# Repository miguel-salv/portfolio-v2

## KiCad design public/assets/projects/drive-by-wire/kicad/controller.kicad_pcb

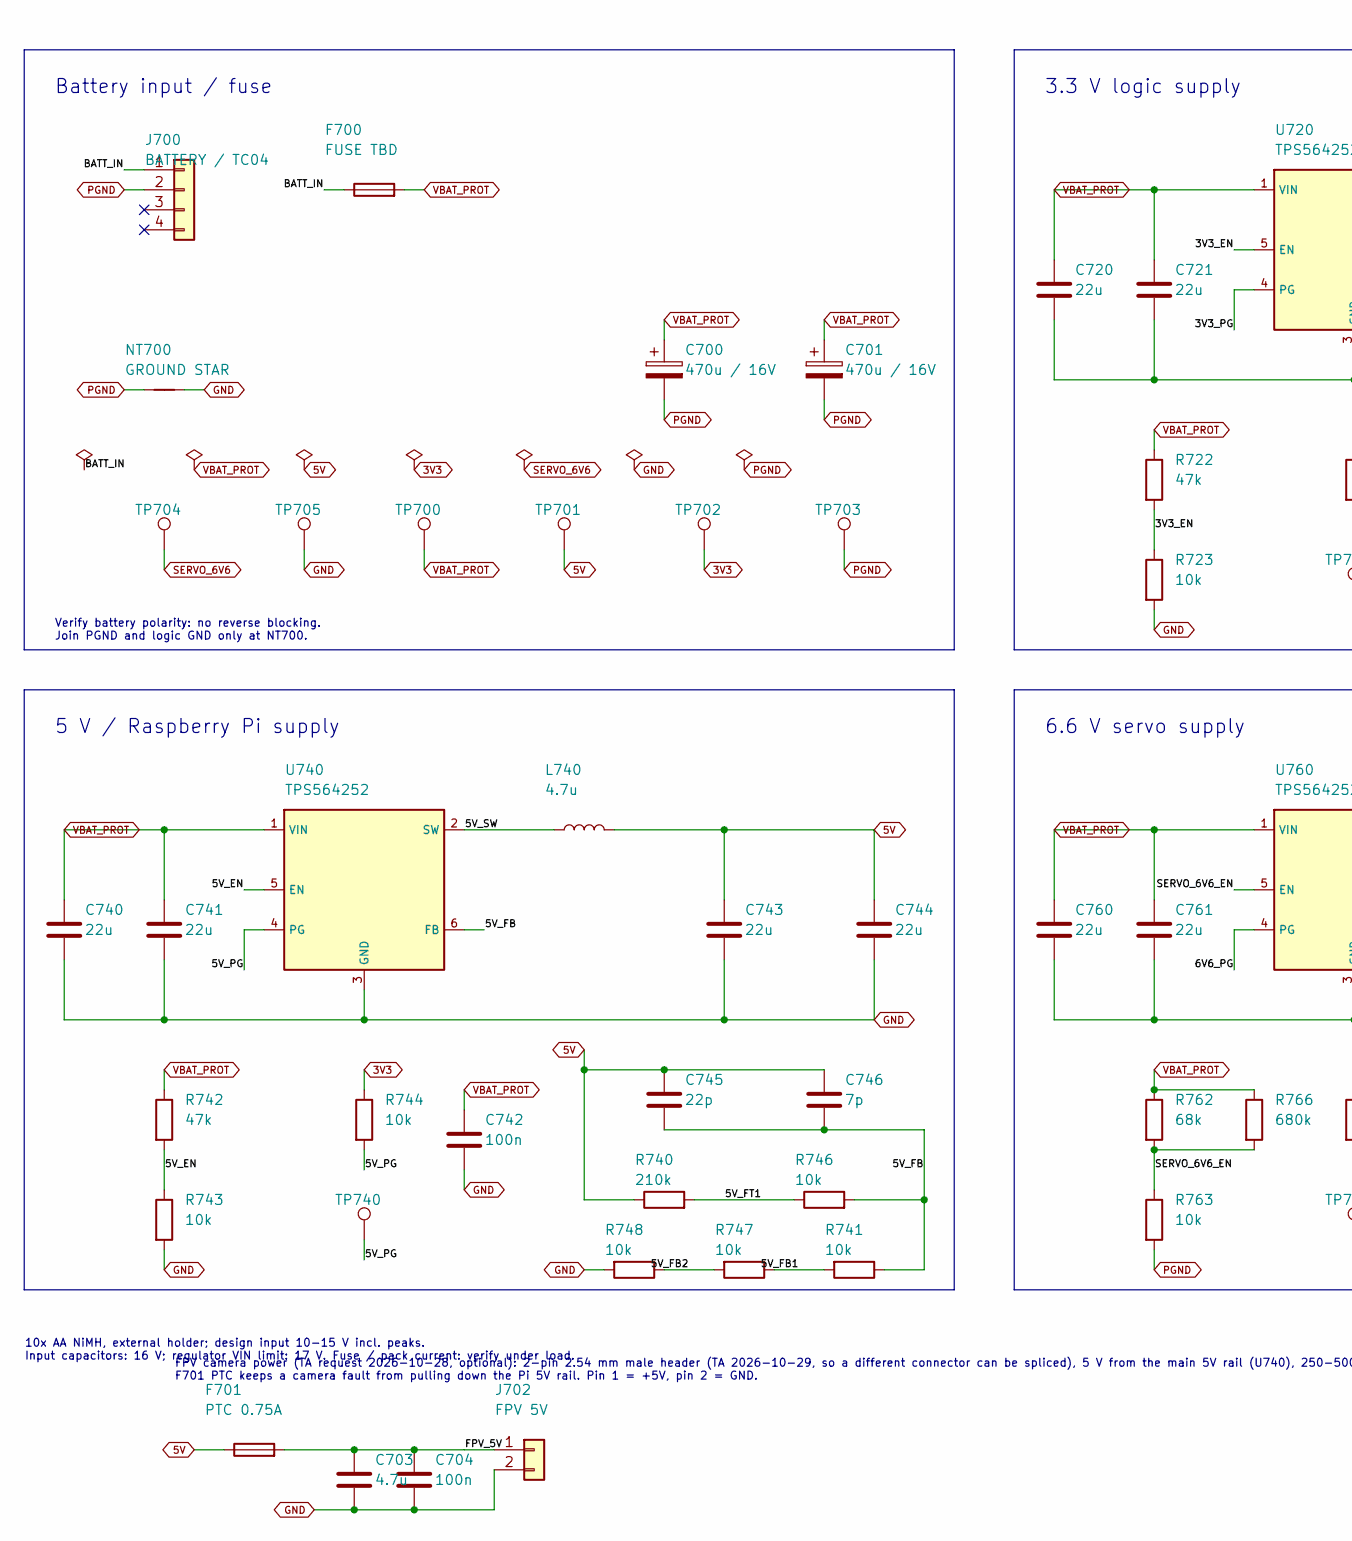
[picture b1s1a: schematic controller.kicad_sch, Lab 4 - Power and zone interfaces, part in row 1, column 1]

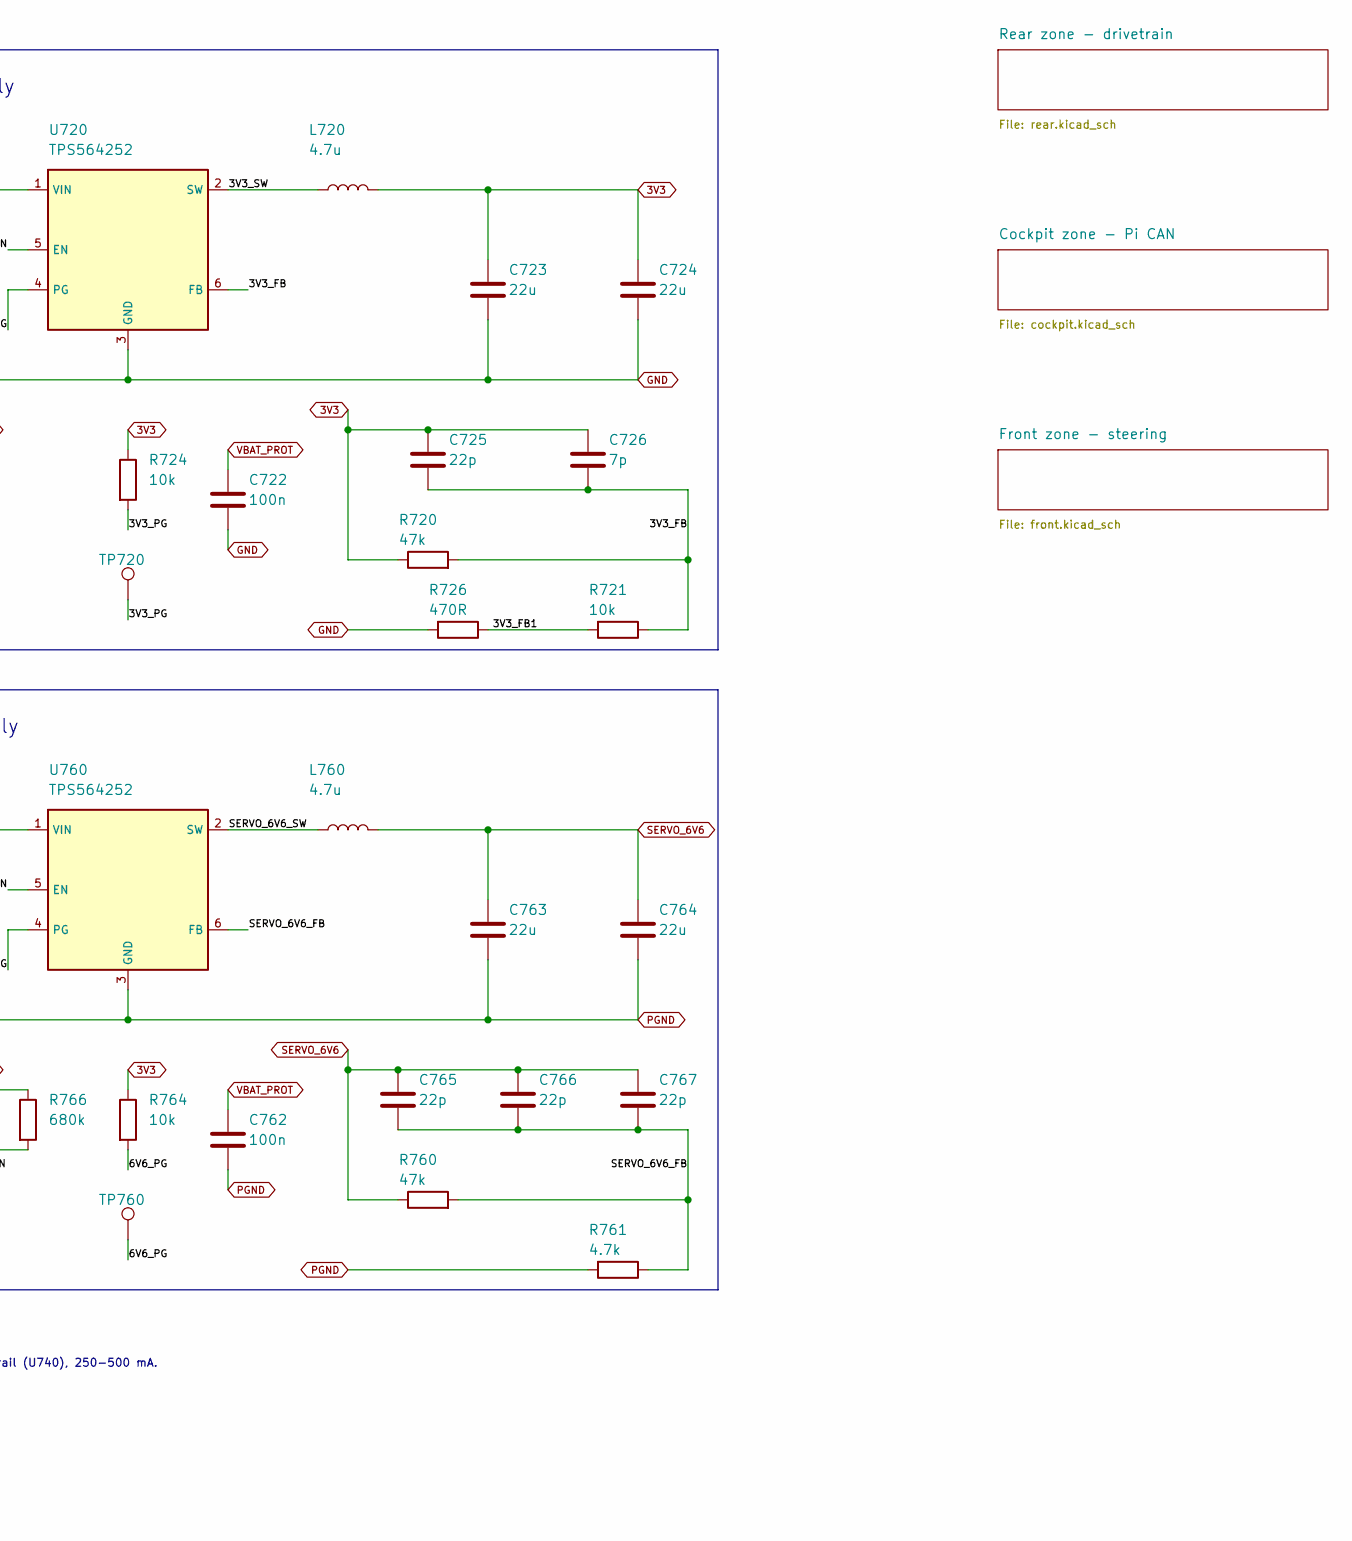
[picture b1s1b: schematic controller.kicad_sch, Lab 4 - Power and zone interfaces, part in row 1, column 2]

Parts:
C700, C701: 470u / 16V; CP_Kemet_A768_KS_D8x12.2; Rating 470uF 16V polymer, 8x12.2mm; 17mOhm; 2.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; MPN A768KS477M1CLAE017; LCSC C1517690
C703: 4.7u; C_0805_2012Metric; Rating 22u; official v2 stock; 22u/4.7u 0805, 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; MPN GRM219R61E475KA73D; LCSC N/A - manual / unresolved
C704, C722, C742, C762: 100n; C_0603_1608Metric; Rating 100n; official v2 stock; 22u/4.7u 0805,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; MPN KGM15AR71C104KT; LCSC N/A - manual / unresolved
C720, C721, C723, C724, C740, C741, C743, C744, C760, C761, C763, C764: 22u; C_0805_2012Metric; Rating 22u; official v2 stock; 22u/4.7u 0805, 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; MPN GRM219R61C226ME15L; LCSC N/A - manual / unresolved
C725, C745, C765, C766, C767: 22p; C_0603_1608Metric; Rating 22p; official v2 stock; 22u/4.7u 0805, 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; MPN C0603C220J1GACTU; LCSC N/A - manual / unresolved
C726, C746: 7p; C_0603_1608Metric; Rating 7p; official v2 stock; 22u/4.7u 0805, o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; MPN CL10C070CB8NNNC; LCSC N/A - manual / unresolved
F700: FUSE TBD; Fuseholder_Blade_Mini_Keystone_3568; Rating Mini blade fuse HOLDER; FUSE rating / t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; MPN 3568; LCSC N/A - manual / unresolved
F701: PTC 0.75A; Fuse_1206_3216Metric; Rating PTC resettable fuse 1206: hold 0.75 A, 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; MPN 1206L075THYR; LCSC TBD - verify
J700: BATTERY / TC04; TerminalBlock_Anytek_TC04_1x04_P5.00mm; Rating 4 positions, 5mm; 15A UL; pins1/2 batte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; MPN TC0403620000G; LCSC N/A - manual / unresolved
J702: FPV 5V; PinHeader_1x02_P2.54mm_Vertical; Rating 2.54 mm male header, 2 pin, vertical TH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; MPN 2.54mm male pin header 1x02, vertical (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; LCSC N/A - manual / unresolved
L720, L740, L760: 4.7u; L_Eaton_SDCHA1V8040; Rating 4.7uH +/-20%; Irms5.8A, Isat6.7A at25C;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; MPN SDCHA1V8040-4R7-R; LCSC N/A - manual / unresolved
NT700: GROUND STAR; NetTie-2_SMD_Pad2.0mm; Rating Single PGND/GND star; high-current copp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; MPN PCB copper net tie; LCSC N/A - manual / unresolved
R720, R722, R742, R760: 47k; R_0603_1608Metric; Rating 47k; 0603 0.1W; 22R 5%, others 1%; MPN RC0603FR-0747KL; LCSC N/A - manual / unresolved
R721, R723, R724, R741, R743, R744, R746, R747, R748, R763, R764: 10k; R_0603_1608Metric; Rating 10k; 0603 0.1W; 22R 5%, others 1%; MPN CRCW060310K0FKEA; LCSC N/A - manual / unresolved
R726: 470R; R_0603_1608Metric; Rating 470R; 0603 0.1W; 22R 5%, others 1%; MPN RC0603FR-07470RL; LCSC N/A - manual / unresolved
R740: 210k; R_0603_1608Metric; Rating 210k; 0603 0.1W; 22R 5%, others 1%; MPN CRCW0603210KFKEA; LCSC N/A - manual / unresolved
R761: 4.7k; R_0603_1608Metric; Rating 4.7k; 0603 0.1W; 22R 5%, others 1%; MPN RC0603FR-074K7L; LCSC N/A - manual / unresolved
R762: 68k; R_0603_1608Metric; Rating 68k; 0603 0.1W; 22R 5%, others 1%; MPN RC0603FR-0768KL; LCSC N/A - manual / unresolved
R766: 680k; R_0603_1608Metric; Rating 680k; 0603 0.1W; 22R 5%, others 1%; MPN CRCW0603680KFKEAC; LCSC N/A - manual / unresolved
TP700: VBAT_PROT; TestPoint_Keystone_5015_Micro_Mini; Rating SMD probe hook; hand fit after reflow; MPN 5015; LCSC N/A - manual / unresolved
TP701: 5V; TestPoint_Keystone_5015_Micro_Mini; Rating SMD probe hook; hand fit after reflow; MPN 5015; LCSC N/A - manual / unresolved
TP702: 3V3; TestPoint_Keystone_5015_Micro_Mini; Rating SMD probe hook; hand fit after reflow; MPN 5015; LCSC N/A - manual / unresolved
TP703: PGND; TestPoint_Keystone_5015_Micro_Mini; Rating SMD probe hook; hand fit after reflow; MPN 5015; LCSC N/A - manual / unresolved
TP704: SERVO_6V6; TestPoint_Keystone_5015_Micro_Mini; Rating SMD probe hook; hand fit after reflow; MPN 5015; LCSC N/A - manual / unresolved
TP705: GND; TestPoint_Keystone_5015_Micro_Mini; Rating SMD probe hook; hand fit after reflow; MPN 5015; LCSC N/A - manual / unresolved
TP720: 3V3_PG; TestPoint_Keystone_5015_Micro_Mini; Rating SMD probe hook; hand fit after reflow; MPN 5015; LCSC N/A - manual / unresolved
TP740: 5V_PG; TestPoint_Keystone_5015_Micro_Mini; Rating SMD probe hook; hand fit after reflow; MPN 5015; LCSC N/A - manual / unresolved
TP760: 6V6_PG; TestPoint_Keystone_5015_Micro_Mini; Rating SMD probe hook; hand fit after reflow; MPN 5015; LCSC N/A - manual / unresolved
U720, U740, U760: TPS564252; SOT-563; Rating 3-17V operating, 4A maximum; thermal ve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; MPN TPS564252DRLR; LCSC C19191267

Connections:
3V3: C723.1, C724.1, C725.1, C726.1, L720.2, R720.1, R724.1, R744.1, R764.1, TP702.1 (1_1); also elsewhere on the board
5V: C743.1, C744.1, C745.1, C746.1, F701.1, L740.2, R740.1, TP701.1 (1_1); also elsewhere on the board
/3V3_EN: R722.2, R723.1, U720.5 (EN)
/3V3_FB: C725.2, C726.2, R720.2, R721.1, U720.6 (FB)
/3V3_FB1: R721.2, R726.1
/3V3_PG: R724.2, TP720.1 (1_1), U720.4 (PG)
/3V3_SW: L720.1, U720.2 (SW)
/5V_EN: R742.2, R743.1, U740.5 (EN)
/5V_FB: C745.2, C746.2, R741.1, R746.2, U740.6 (FB)
/5V_FB1: R741.2, R747.1
/5V_FB2: R747.2, R748.1
/5V_FT1: R740.2, R746.1
/5V_PG: R744.2, TP740.1 (1_1), U740.4 (PG)
/5V_SW: L740.1, U740.2 (SW)
/6V6_PG: R764.2, TP760.1 (1_1), U760.4 (PG)
/BATT_IN: F700.1, J700.1
/FPV_5V: C703.1, C704.1, F701.2, J702.1
/SERVO_6V6_EN: R762.2, R763.1, R766.2, U760.5 (EN)
/SERVO_6V6_FB: C765.2, C766.2, C767.2, R760.2, R761.1, U760.6 (FB)
/SERVO_6V6_SW: L760.1, U760.2 (SW)
GND: C703.2, C704.2, C720.2, C721.2, C722.2, C723.2, C724.2, C740.2, C741.2, C742.2, C743.2, C744.2, J702.2, NT700.2, R723.2, R726.2, R743.2, R748.2, TP705.1 (1_1), U720.3 (GND), U740.3 (GND); also elsewhere on the board
PGND: C700.2, C701.2, C760.2, C761.2, C762.2, C763.2, C764.2, J700.2, NT700.1, R761.2, R763.2, TP703.1 (1_1), U760.3 (GND); also elsewhere on the board
SERVO_6V6: C763.1, C764.1, C765.1, C766.1, C767.1, L760.2, R760.1, TP704.1 (1_1); also elsewhere on the board
VBAT_PROT: C700.1, C701.1, C720.1, C721.1, C722.1, C740.1, C741.1, C742.1, C760.1, C761.1, C762.1, F700.2, R722.1, R742.1, R762.1, R766.1, TP700.1 (1_1), U720.1 (VIN), U740.1 (VIN), U760.1 (VIN); also elsewhere on the board

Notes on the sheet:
Verify battery polarity: no reverse blocking. Join PGND and logic GND only at NT700.
5 V / Raspberry Pi supply
3.3 V logic supply
Battery input / fuse
6.6 V servo supply
10x AA NiMH, external holder; design input 10-15 V incl. peaks. Input capacitors: 16 V; regulator VIN limit: 17 V. Fuse / pack current: verify under load.
FPV camera power (TA request 2026-10-28, optional): 2-pin 2.54 mm male header (TA 2026-10-29, so a different connector can be spliced), 5 V from the main 5V rail (U740), 250-500 mA. F701 PTC keeps a camera fault from pulling down the Pi 5V rail. Pin 1 = +5V, pin 2 = GND.

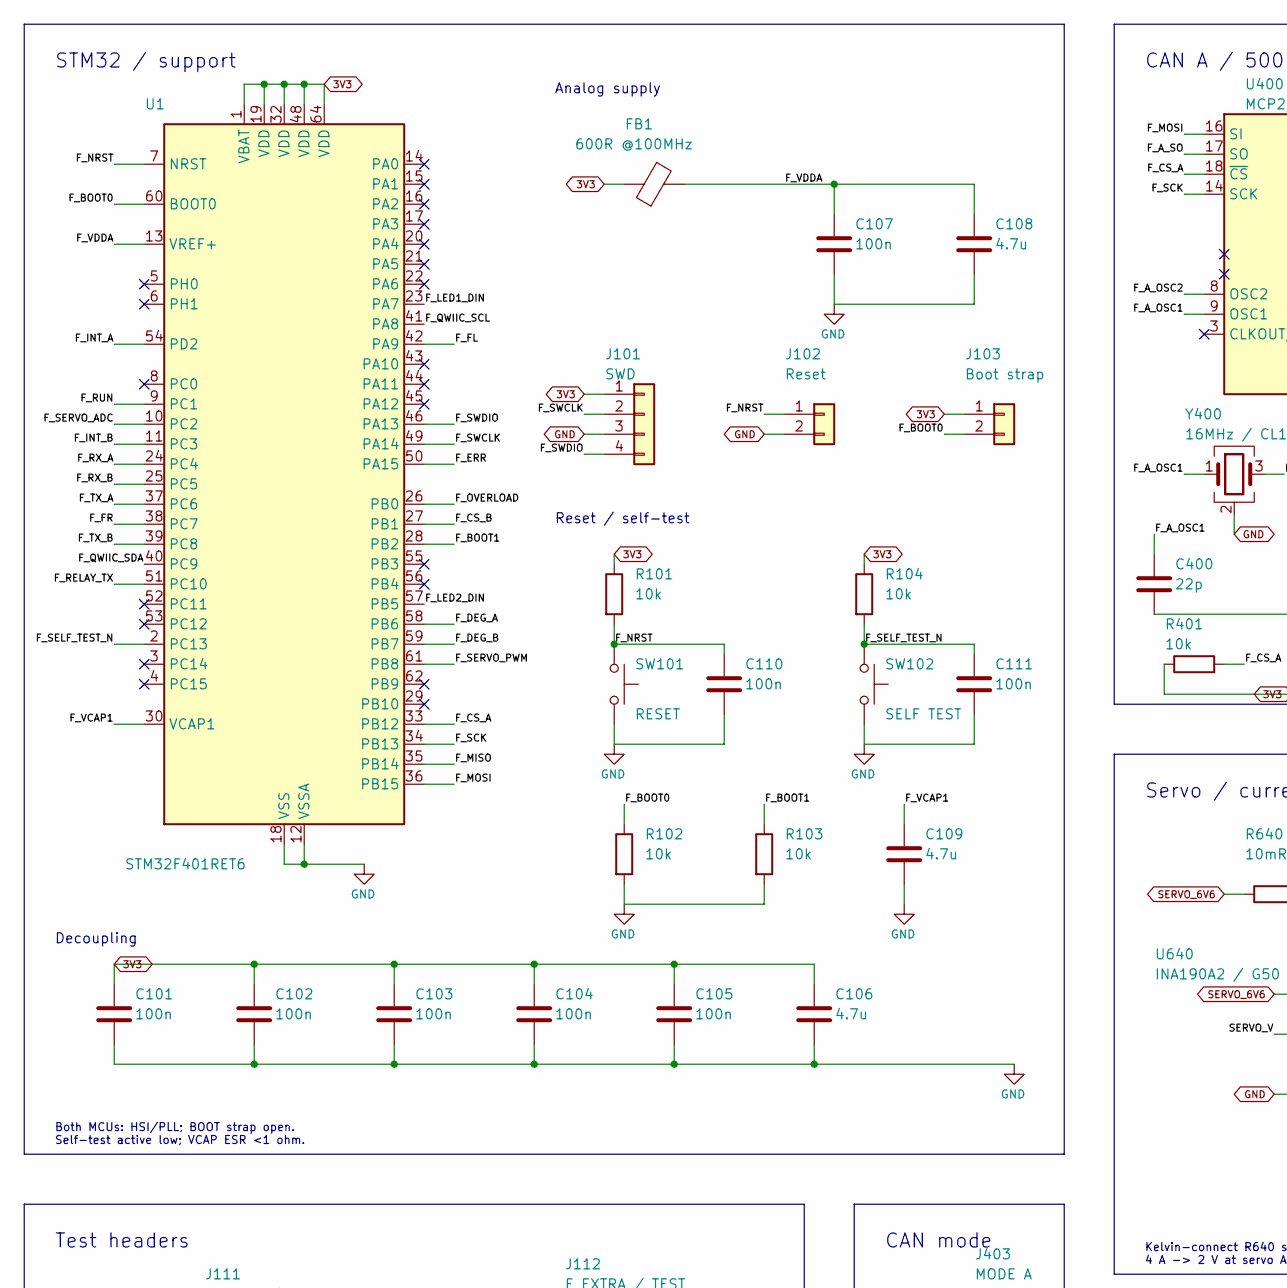
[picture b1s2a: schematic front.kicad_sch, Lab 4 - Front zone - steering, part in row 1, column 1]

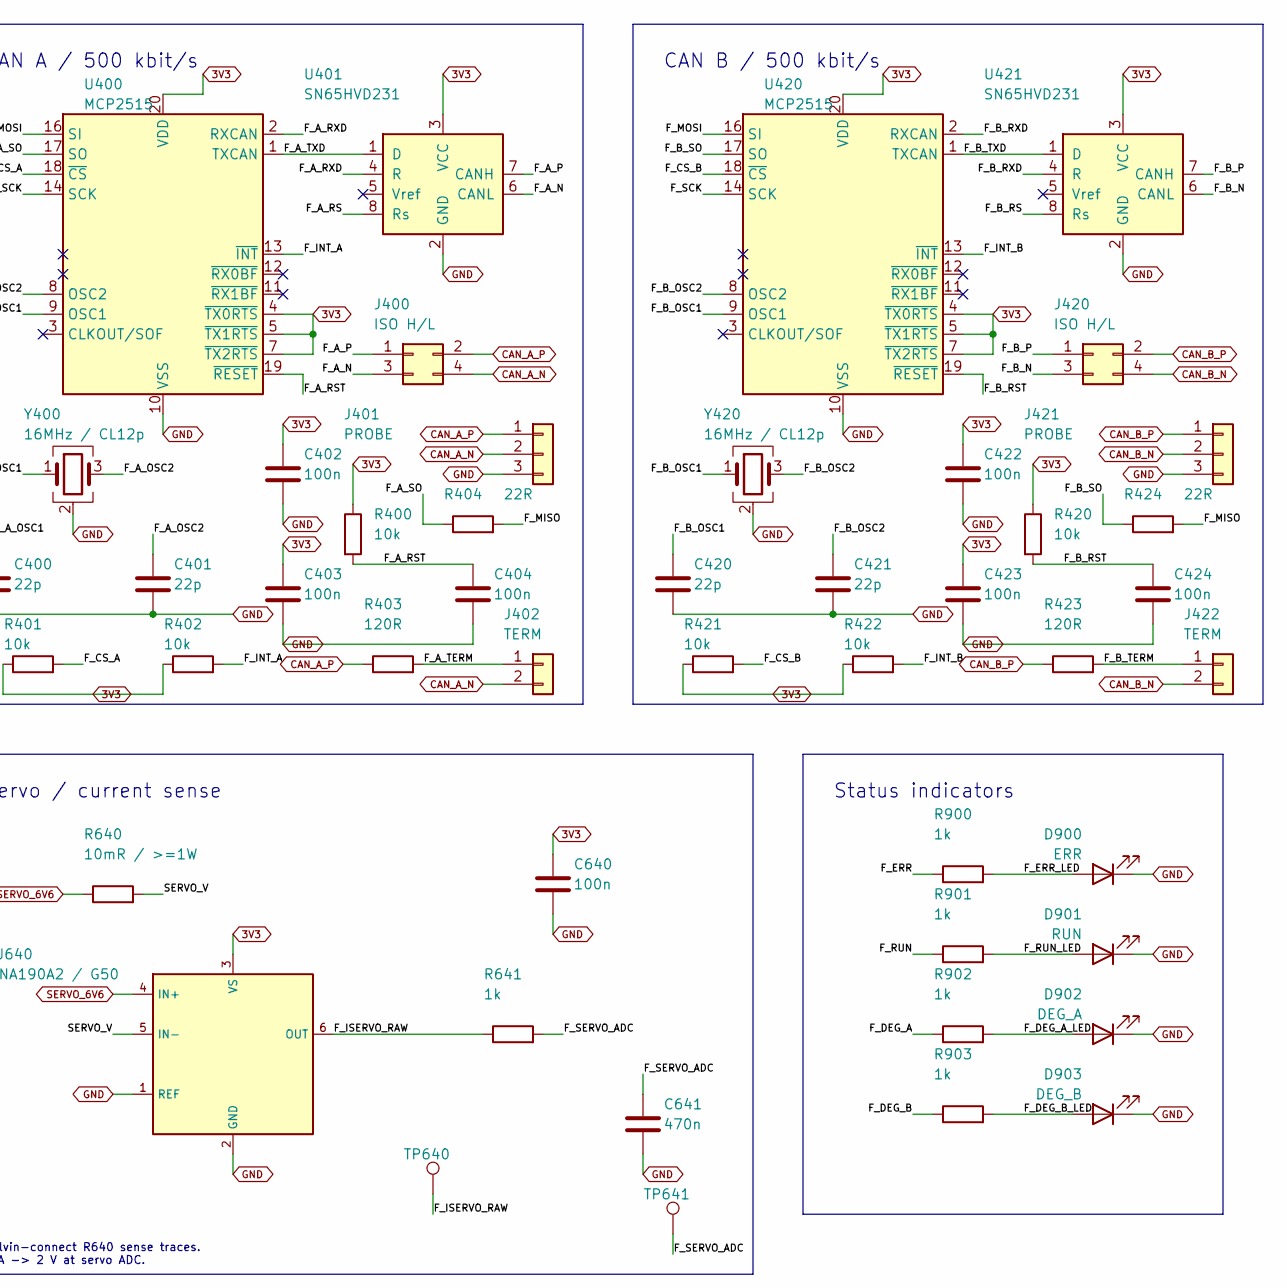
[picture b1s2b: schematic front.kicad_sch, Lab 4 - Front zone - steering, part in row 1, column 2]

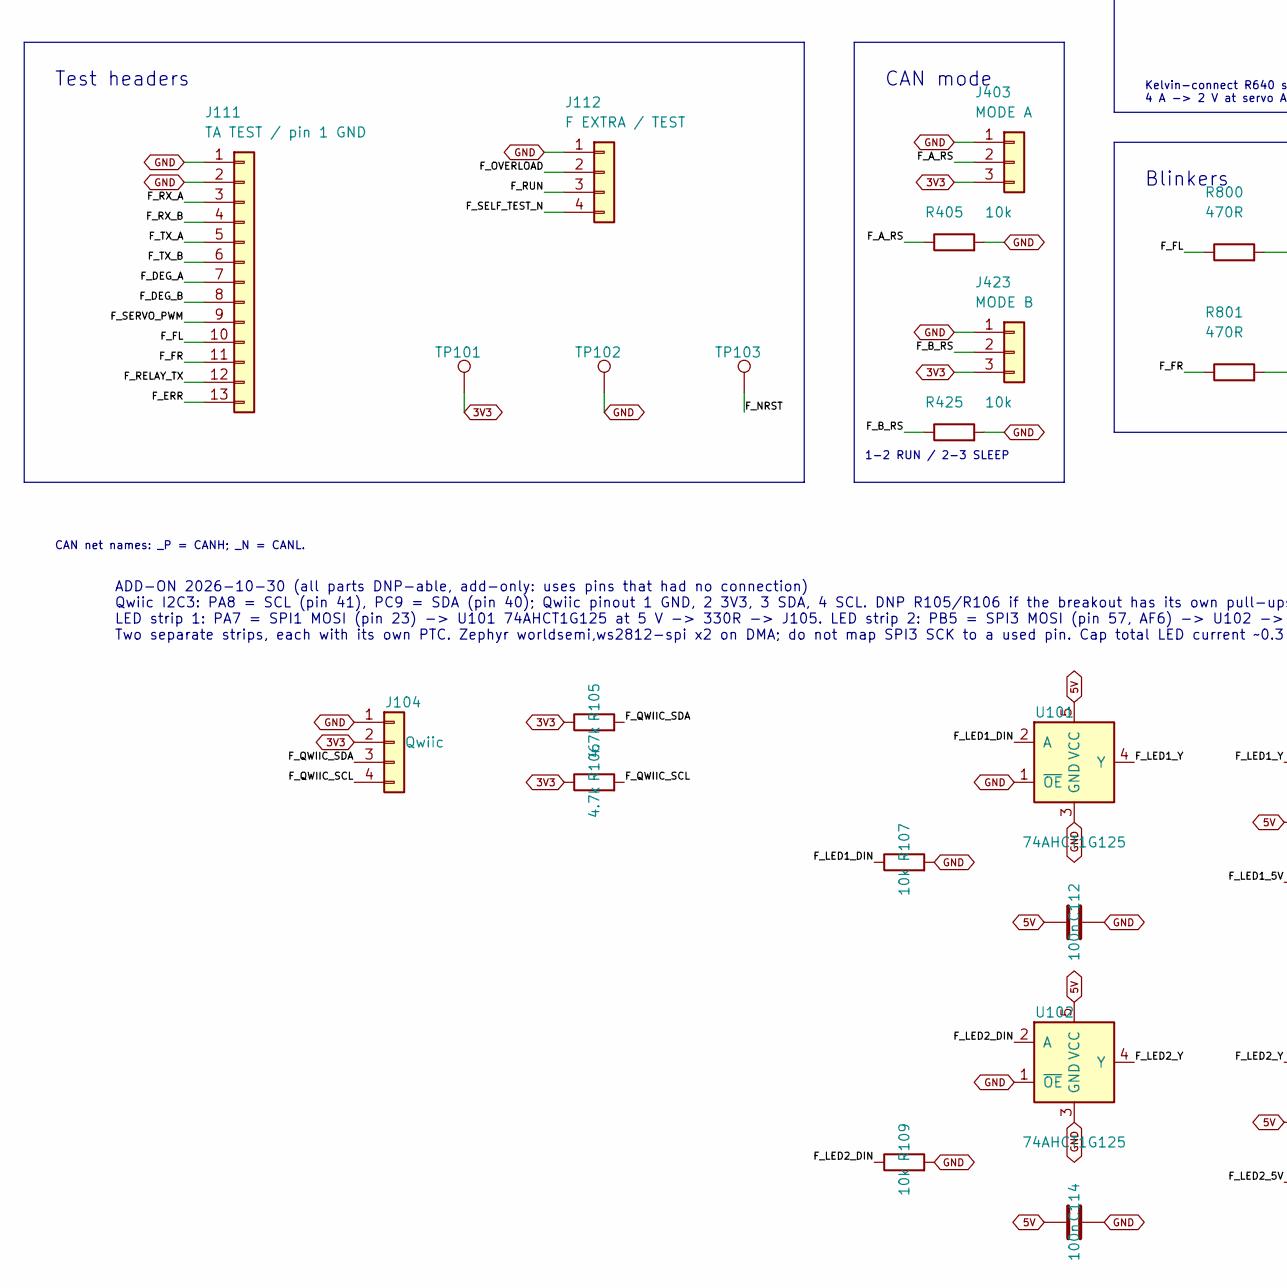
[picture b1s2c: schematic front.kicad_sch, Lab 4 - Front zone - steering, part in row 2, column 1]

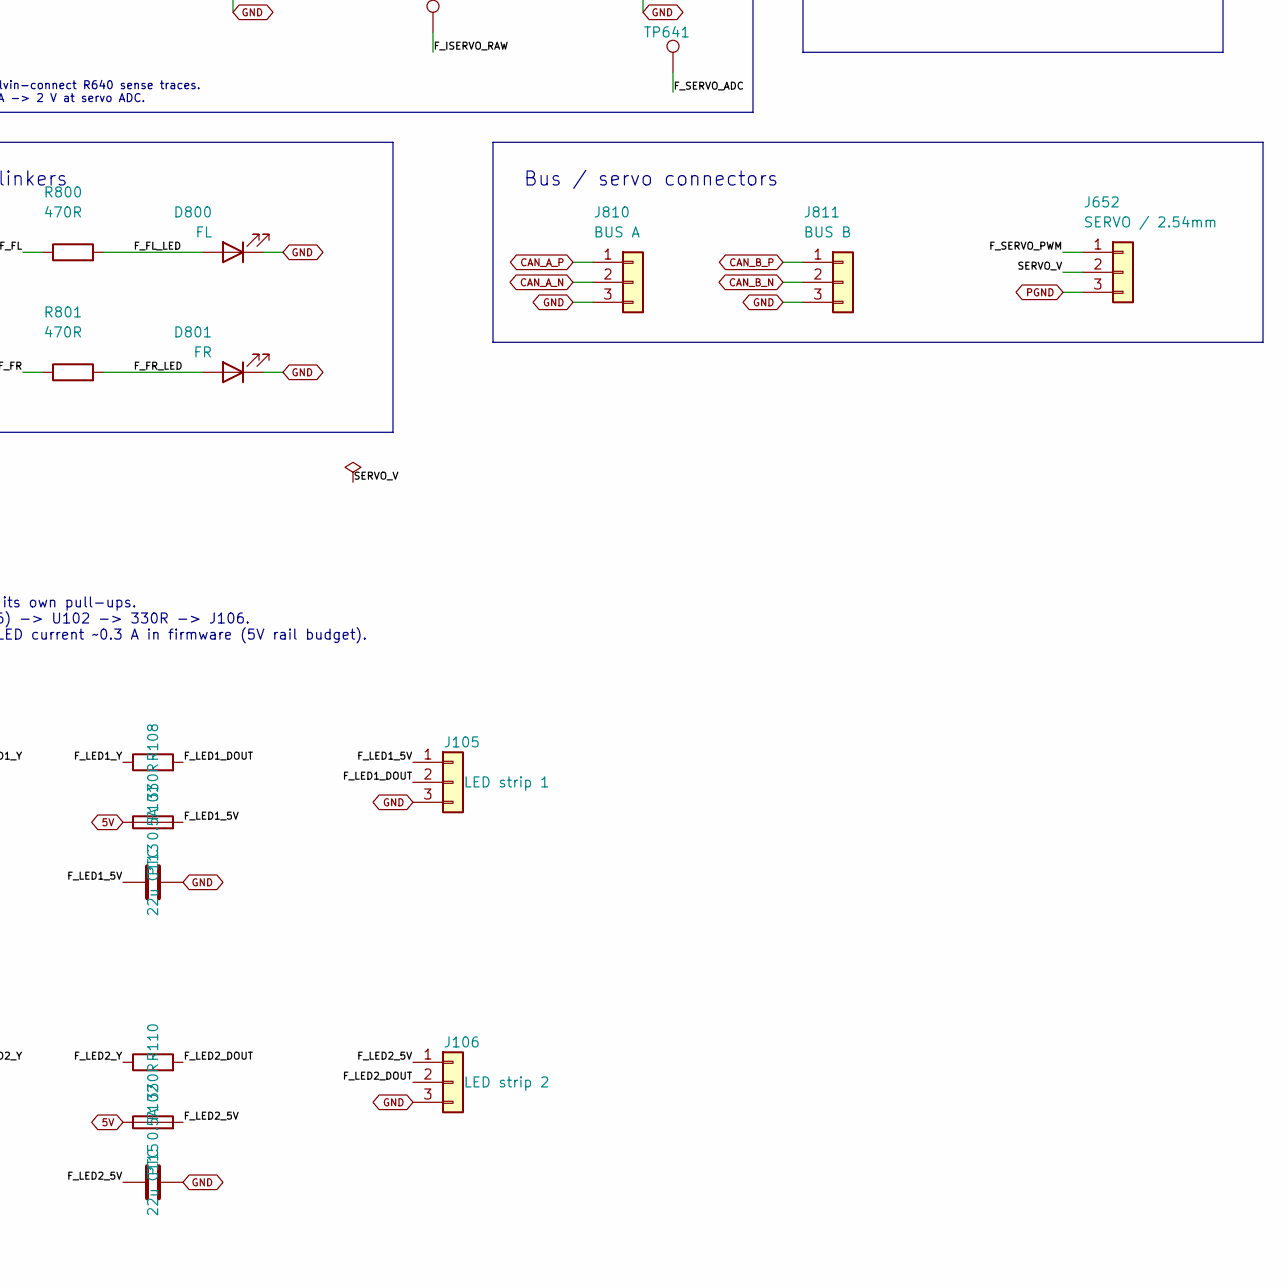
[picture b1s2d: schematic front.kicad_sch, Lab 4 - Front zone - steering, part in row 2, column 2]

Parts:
C101, C102, C103, C104, C105, C107, C110, C111, C402, C403, C404, C422, C423, C424, C640: 100n; C_0603_1608Metric; Rating 100n; official v2 stock; 22u/4.7u 0805,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; MPN KGM15AR71C104KT; LCSC N/A - manual / unresolved
C106, C108, C109: 4.7u; C_0805_2012Metric; Rating 4.7u; official v2 stock; 22u/4.7u 0805,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; MPN GRM21BR71C475KE51L; LCSC N/A - manual / unresolved
C112, C114: 100n; C_0603_1608Metric; Rating Decoupling at buffer VCC; MPN CC0603KRX7R9BB104; JLCPCB Class Verify at order
C113, C115: 22u; C_0805_2012Metric; Rating Local bulk for LED strip inrush; MPN CL21A226MAQNNNE; JLCPCB Class Verify at order
C400, C401, C420, C421: 22p; C_0603_1608Metric; Rating 22p; official v2 stock; 22u/4.7u 0805, 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; MPN C0603C220J1GACTU; LCSC N/A - manual / unresolved
C641: 470n; C_0603_1608Metric; Rating 470n; official v2 stock; 22u/4.7u 0805,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; MPN CL10B474KO8NNND; LCSC N/A - manual / unresolved
D800: FL; LED_D3.0mm; Rating Yellow 3mm radial; 470R limits current; MPN 151031YS06000; LCSC N/A - manual / unresolved
D801: FR; LED_D3.0mm; Rating Yellow 3mm radial; 470R limits current; MPN 151031YS06000; LCSC N/A - manual / unresolved
D900: ERR; LED_0603_1608Metric; Rating 0603; green RUN / red ERR and DEG; MPN LTST-C190KRKT; LCSC N/A - manual / unresolved
D901: RUN; LED_0603_1608Metric; Rating 0603; green RUN / red ERR and DEG; MPN LTST-C190GKT; LCSC N/A - manual / unresolved
D902: DEG_A; LED_0603_1608Metric; Rating 0603; green RUN / red ERR and DEG; MPN LTST-C190KRKT; LCSC N/A - manual / unresolved
D903: DEG_B; LED_0603_1608Metric; Rating 0603; green RUN / red ERR and DEG; MPN LTST-C190KRKT; LCSC N/A - manual / unresolved
F101, F102: PTC 0.5A; Fuse_1206_3216Metric; Rating PTC hold 0.5 A, trip 1.0 A, 30 V; prote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; MPN BSMD1206-050-30V; JLCPCB Class Verify at order
FB1: 600R @100MHz; L_0603_1608Metric; Rating 0603; 600ohm@100MHz,500mA; 0.35ohm maxD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; MPN 742863160; LCSC N/A - manual / unresolved
J101: SWD; PinHeader_1x04_P2.54mm_Vertical; Rating See footprint and netlist for pin count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; MPN 2.54mm pin header; cut to length; LCSC N/A - manual / unresolved
J102: Reset; PinHeader_1x02_P2.54mm_Vertical; Rating See footprint and netlist for pin count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; MPN 2.54mm pin header; cut to length; LCSC N/A - manual / unresolved
J103: Boot strap; PinHeader_1x02_P2.54mm_Vertical; Rating See footprint and netlist for pin count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; MPN 2.54mm pin header; cut to length; LCSC N/A - manual / unresolved
J104: Qwiic; JST_SH_SM04B-SRSS-TB_1x04-1MP_P1.00mm_Horizontal; Rating Qwiic / STEMMA QT: 1 GND, 2 3V3, 3 SDA,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; MPN SM04B-SRSS-TB(LF)(SN); JLCPCB Class Verify at order
J105: LED strip 1; PinHeader_1x03_P2.54mm_Vertical; Rating 1 = 5V (fused), 2 = DATA (5 V logic), 3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; MPN 2.54-1*3P (male, straight); JLCPCB Class Verify at order
J106: LED strip 2; PinHeader_1x03_P2.54mm_Vertical; Rating 1 = 5V (fused), 2 = DATA (5 V logic), 3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; MPN 2.54-1*3P (male, straight); JLCPCB Class Verify at order
J111: TA TEST / pin 1 GND; PinHeader_1x13_P2.54mm_Vertical; Rating See footprint and netlist for pin count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; MPN 2.54mm pin header; cut to length; LCSC N/A - manual / unresolved
J112: F EXTRA / TEST; PinHeader_1x04_P2.54mm_Vertical; Rating See footprint and netlist for pin count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; MPN 2.54mm pin header; cut to length; LCSC N/A - manual / unresolved
J400, J420: ISO H/L; PinHeader_2x02_P2.54mm_Vertical; Rating See footprint and netlist for pin count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; MPN 2.54mm pin header; cut to length; LCSC N/A - manual / unresolved
J401, J421: PROBE; PinHeader_1x03_P2.54mm_Vertical; Rating See footprint and netlist for pin count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; MPN 2.54mm pin header; cut to length; LCSC N/A - manual / unresolved
J402, J422: TERM; PinHeader_1x02_P2.54mm_Vertical; Rating See footprint and netlist for pin count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; MPN 2.54mm pin header; cut to length; LCSC N/A - manual / unresolved
J403: MODE A; PinHeader_1x03_P2.54mm_Vertical; Rating See footprint and netlist for pin count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; MPN 2.54mm pin header; cut to length; LCSC N/A - manual / unresolved
J423: MODE B; PinHeader_1x03_P2.54mm_Vertical; Rating See footprint and netlist for pin count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; MPN 2.54mm pin header; cut to length; LCSC N/A - manual / unresolved
J652: SERVO / 2.54mm; PinHeader_1x03_P2.54mm_Vertical; Rating Cut 3 positions from ordinary 2.54mm st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; MPN 2.54mm pin header; cut to length; LCSC N/A - manual / unresolved
J810: BUS A; PinHeader_1x03_P2.54mm_Vertical; Rating See footprint and netlist for pin count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; MPN 2.54mm pin header; cut to length; LCSC N/A - manual / unresolved
J811: BUS B; PinHeader_1x03_P2.54mm_Vertical; Rating See footprint and netlist for pin count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; MPN 2.54mm pin header; cut to length; LCSC N/A - manual / unresolved
R101, R102, R103, R104, R400, R401, R402, R405, R420, R421, R422, R425: 10k; R_0603_1608Metric; Rating 10k; 0603 0.1W; 22R 5%, others 1%; MPN CRCW060310K0FKEA; LCSC N/A - manual / unresolved
R105: 4.7k; R_0603_1608Metric; Rating I2C3 SDA pull-up; DNP if breakout has i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; MPN 0603WAF4701T5E; JLCPCB Class Verify at order
R106: 4.7k; R_0603_1608Metric; Rating I2C3 SCL pull-up; DNP if breakout has i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; MPN 0603WAF4701T5E; JLCPCB Class Verify at order
R107, R109: 10k; R_0603_1608Metric; Rating Pull-down: keeps LED data low while the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; MPN 0603WAF1002T5E; JLCPCB Class Verify at order
R108, R110: 330R; R_0603_1608Metric; Rating Series resistor on LED data (ringing an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; MPN RC0603FR-07330RL; JLCPCB Class Verify at order
R403, R423: 120R; R_0603_1608Metric; Rating 120R; 0603 0.1W; 22R 5%, others 1%; MPN RC0603FR-07120RL; LCSC N/A - manual / unresolved
R404, R424: 22R; R_0603_1608Metric; Rating 22R; 0603 0.1W; 22R 5%, others 1%; MPN CRGCQ0603J22R; LCSC N/A - manual / unresolved
R640: 10mR / >=1W; R_2512_6332Metric; Rating 10mOhm 1% 3W at70C; Kelvin pickup requi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; MPN WSLP2512R0100FEA; LCSC N/A - manual / unresolved
R641, R900, R901, R902, R903: 1k; R_0603_1608Metric; Rating 1k; 0603 0.1W; 22R 5%, others 1%; MPN ERJ-3EKF1001V; LCSC N/A - manual / unresolved
R800, R801: 470R; R_0603_1608Metric; Rating 470R; 0603 0.1W; 22R 5%, others 1%; MPN RC0603FR-07470RL; LCSC N/A - manual / unresolved
SW101: RESET; SW_GCT_SWT0210; Rating Course part, custom two-net footprint v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; MPN SWT0210-045026GSA; LCSC N/A - manual / unresolved
SW102: SELF TEST; SW_GCT_SWT0210; Rating Course part, custom two-net footprint v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; MPN SWT0210-045026GSA; LCSC N/A - manual / unresolved
TP101: 3V3; TestPoint_Keystone_5015_Micro_Mini; Rating SMD probe hook; hand fit after reflow; MPN 5015; LCSC N/A - manual / unresolved
TP102: GND; TestPoint_Keystone_5015_Micro_Mini; Rating SMD probe hook; hand fit after reflow; MPN 5015; LCSC N/A - manual / unresolved
TP103: F_NRST; TestPoint_Keystone_5015_Micro_Mini; Rating SMD probe hook; hand fit after reflow; MPN 5015; LCSC N/A - manual / unresolved
TP640: F_ISERVO_RAW; TestPoint_Keystone_5015_Micro_Mini; Rating SMD probe hook; hand fit after reflow; MPN 5015; LCSC N/A - manual / unresolved
TP641: F_SERVO_ADC; TestPoint_Keystone_5015_Micro_Mini; Rating SMD probe hook; hand fit after reflow; MPN 5015; LCSC N/A - manual / unresolved
U1: STM32F401RET6; LQFP-64_10x10mm_P0.5mm_Pin1_Inboard; Rating LQFP64, bare MCU; TR tape/reel suffix; MPN STM32F401RET6TR; LCSC N/A - manual / unresolved
U101, U102: 74AHCT1G125; SOT-23-5; Rating 3.3 V MCU to 5 V WS2812 DIN (WS2812 VIH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; MPN SN74AHCT1G125DBVR; JLCPCB Class Verify at order
U400, U420: MCP2515; TSSOP-20_4.4x6.5mm_P0.65mm; Rating TSSOP20; 16MHz at 3V3; MPN MCP2515T-I/ST; LCSC C185941
U401, U421: SN65HVD231; SOIC-8_3.9x4.9mm_P1.27mm; Rating SOIC8; Rs mode 1-2 RUN, 2-3 SLEEP. 10k 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; MPN SN65HVD231DR; LCSC C129257
U640: INA190A2 / G50; SOT-363_SC-70-6; Rating SC70-6; gain50; outside course list; MPN INA190A2IDCKR; LCSC C2870223
Y400, Y420: 16MHz / CL12p; Crystal_SMD_3225-4Pin_3.2x2.5mm; Rating 16MHz CL12pF 80ohm; 3225 four pads; par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; MPN CX3225SB16000H0FLJCC; LCSC N/A - course stock

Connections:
3V3: C101.1, C102.1, C103.1, C104.1, C105.1, C106.1, C402.1, C403.1, C422.1, C423.1, C640.1, FB1.1, J101.1, J103.1, J104.2, J403.3, J423.3, R101.1, R104.1, R105.1, R106.1, R400.1, R401.1, R402.1, R420.1, R421.1, R422.1, TP101.1 (1_1), U1.1 (VBAT), U1.19 (VDD), U1.32 (VDD), U1.48 (VDD), U1.64 (VDD), U400.4 (~TX0RTS), U400.5 (~TX1RTS), U400.7 (~TX2RTS), U400.20 (VDD), U401.3 (VCC), U420.4 (~TX0RTS), U420.5 (~TX1RTS), U420.7 (~TX2RTS), U420.20 (VDD), U421.3 (VCC), U640.3 (VS); also elsewhere on the board
5V: C112.1, C114.1, F101.1, F102.1, U101.5 (VCC), U102.5 (VCC); also elsewhere on the board
/Front zone - steering/F_A_N: J400.3, U401.6 (CANL)
/Front zone - steering/F_A_OSC1: C400.1, U400.9 (OSC1), Y400.1
/Front zone - steering/F_A_OSC2: C401.1, U400.8 (OSC2), Y400.3
/Front zone - steering/F_A_P: J400.1, U401.7 (CANH)
/Front zone - steering/F_A_RS: J403.2, R405.1, U401.8 (Rs)
/Front zone - steering/F_A_RST: C404.1, R400.2, U400.19 (~RESET)
/Front zone - steering/F_A_RXD: U400.2 (RXCAN), U401.4 (R)
/Front zone - steering/F_A_SO: R404.1, U400.17 (SO)
/Front zone - steering/F_A_TERM: J402.1, R403.2
/Front zone - steering/F_A_TXD: U400.1 (TXCAN), U401.1 (D)
/Front zone - steering/F_BOOT0: J103.2, R102.1, U1.60 (BOOT0)
/Front zone - steering/F_BOOT1: R103.1, U1.28 (PB2)
/Front zone - steering/F_B_N: J420.3, U421.6 (CANL)
/Front zone - steering/F_B_OSC1: C420.1, U420.9 (OSC1), Y420.1
/Front zone - steering/F_B_OSC2: C421.1, U420.8 (OSC2), Y420.3
/Front zone - steering/F_B_P: J420.1, U421.7 (CANH)
/Front zone - steering/F_B_RS: J423.2, R425.1, U421.8 (Rs)
/Front zone - steering/F_B_RST: C424.1, R420.2, U420.19 (~RESET)
/Front zone - steering/F_B_RXD: U420.2 (RXCAN), U421.4 (R)
/Front zone - steering/F_B_SO: R424.1, U420.17 (SO)
/Front zone - steering/F_B_TERM: J422.1, R423.2
/Front zone - steering/F_B_TXD: U420.1 (TXCAN), U421.1 (D)
/Front zone - steering/F_CS_A: R401.2, U1.33 (PB12), U400.18 (~CS)
/Front zone - steering/F_CS_B: R421.2, U1.27 (PB1), U420.18 (~CS)
/Front zone - steering/F_DEG_A: J111.7, R902.1, U1.58 (PB6)
/Front zone - steering/F_DEG_A_LED: D902.2 (A), R902.2
/Front zone - steering/F_DEG_B: J111.8, R903.1, U1.59 (PB7)
/Front zone - steering/F_DEG_B_LED: D903.2 (A), R903.2
/Front zone - steering/F_ERR: J111.13, R900.1, U1.50 (PA15)
/Front zone - steering/F_ERR_LED: D900.2 (A), R900.2
/Front zone - steering/F_FL: J111.10, R800.1, U1.42 (PA9)
/Front zone - steering/F_FL_LED: D800.2 (A), R800.2
/Front zone - steering/F_FR: J111.11, R801.1, U1.38 (PC7)
/Front zone - steering/F_FR_LED: D801.2 (A), R801.2
/Front zone - steering/F_INT_A: R402.2, U1.54 (PD2), U400.13 (~INT)
/Front zone - steering/F_INT_B: R422.2, U1.11 (PC3), U420.13 (~INT)
/Front zone - steering/F_ISERVO_RAW: R641.1, TP640.1 (1_1), U640.6 (OUT)
/Front zone - steering/F_LED1_5V: C113.1, F101.2, J105.1
/Front zone - steering/F_LED1_DIN: R107.1, U1.23 (PA7), U101.2 (A)
/Front zone - steering/F_LED1_DOUT: J105.2, R108.2
/Front zone - steering/F_LED1_Y: R108.1, U101.4 (Y)
/Front zone - steering/F_LED2_5V: C115.1, F102.2, J106.1
/Front zone - steering/F_LED2_DIN: R109.1, U1.57 (PB5), U102.2 (A)
/Front zone - steering/F_LED2_DOUT: J106.2, R110.2
/Front zone - steering/F_LED2_Y: R110.1, U102.4 (Y)
/Front zone - steering/F_MISO: R404.2, R424.2, U1.35 (PB14)
/Front zone - steering/F_MOSI: U1.36 (PB15), U400.16 (SI), U420.16 (SI)
/Front zone - steering/F_NRST: C110.1, J102.1, R101.2, SW101.1, TP103.1 (1_1), U1.7 (NRST)
/Front zone - steering/F_OVERLOAD: J112.2, U1.26 (PB0)
/Front zone - steering/F_QWIIC_SCL: J104.4, R106.2, U1.41 (PA8)
/Front zone - steering/F_QWIIC_SDA: J104.3, R105.2, U1.40 (PC9)
/Front zone - steering/F_RELAY_TX: J111.12, U1.51 (PC10)
/Front zone - steering/F_RUN: J112.3, R901.1, U1.9 (PC1)
/Front zone - steering/F_RUN_LED: D901.2 (A), R901.2
/Front zone - steering/F_RX_A: J111.3, U1.24 (PC4)
/Front zone - steering/F_RX_B: J111.4, U1.25 (PC5)
/Front zone - steering/F_SCK: U1.34 (PB13), U400.14 (SCK), U420.14 (SCK)
/Front zone - steering/F_SELF_TEST_N: C111.1, J112.4, R104.2, SW102.1, U1.2 (PC13)
/Front zone - steering/F_SERVO_ADC: C641.1, R641.2, TP641.1 (1_1), U1.10 (PC2)
/Front zone - steering/F_SERVO_PWM: J111.9, J652.1, U1.61 (PB8)
/Front zone - steering/F_SWCLK: J101.2, U1.49 (PA14)
/Front zone - steering/F_SWDIO: J101.4, U1.46 (PA13)
/Front zone - steering/F_TX_A: J111.5, U1.37 (PC6)
/Front zone - steering/F_TX_B: J111.6, U1.39 (PC8)
/Front zone - steering/F_VCAP1: C109.1, U1.30 (VCAP1)
/Front zone - steering/F_VDDA: C107.1, C108.1, FB1.2, U1.13 (VREF+)
/Front zone - steering/SERVO_V: J652.2, R640.2, U640.5 (IN-)
CAN_A_N: J400.4, J401.2, J402.2, J810.2; also elsewhere on the board
CAN_A_P: J400.2, J401.1, J810.1, R403.1; also elsewhere on the board
CAN_B_N: J420.4, J421.2, J422.2, J811.2; also elsewhere on the board
CAN_B_P: J420.2, J421.1, J811.1, R423.1; also elsewhere on the board
GND: C101.2, C102.2, C103.2, C104.2, C105.2, C106.2, C107.2, C108.2, C109.2, C110.2, C111.2, C112.2, C113.2, C114.2, C115.2, C400.2, C401.2, C402.2, C403.2, C404.2, C420.2, C421.2, C422.2, C423.2, C424.2, C640.2, C641.2, D800.1 (K), D801.1 (K), D900.1 (K), D901.1 (K), D902.1 (K), D903.1 (K), J101.3, J102.2, J104.1, J105.3, J106.3, J111.1, J111.2, J112.1, J401.3, J403.1, J421.3, J423.1, J810.3, J811.3, R102.2, R103.2, R107.2, R109.2, R405.2, R425.2, SW101.2, SW102.2, TP102.1 (1_1), U1.12 (VSSA), U1.18 (VSS), U1.31 (VSS), U1.47 (VSS), U1.63 (VSS), U101.1 (~OE), U101.3 (GND), U102.1 (~OE), U102.3 (GND), U400.10 (VSS), U401.2 (GND), U420.10 (VSS), U421.2 (GND), U640.1 (REF), U640.2 (GND), Y400.2 (G), Y400.4 (G), Y420.2 (G), Y420.4 (G); also elsewhere on the board
PGND: J652.3; also elsewhere on the board
SERVO_6V6: R640.1, U640.4 (IN+); also elsewhere on the board

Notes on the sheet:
CAN A / 500 kbit/s
Status indicators
Servo / current sense
Kelvin-connect R640 sense traces. 4 A -> 2 V at servo ADC.
Decoupling
1-2 RUN / 2-3 SLEEP
CAN mode
Analog supply
Test headers
Reset / self-test
CAN B / 500 kbit/s
STM32 / support
Bus / servo connectors
CAN net names: _P = CANH; _N = CANL.
Blinkers
Both MCUs: HSI/PLL; BOOT strap open. Self-test active low; VCAP ESR <1 ohm.
ADD-ON 2026-10-30 (all parts DNP-able, add-only: uses pins that had no connection) Qwiic I2C3: PA8 = SCL (pin 41), PC9 = SDA (pin 40); Qwiic pinout 1 GND, 2 3V3, 3 SDA, 4 SCL. DNP R105/R106 if the breakout has its own pull-ups. LED strip 1: PA7 = SPI1 MOSI (pin 23) -> U101 74AHCT1G125 at 5 V -> 330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
